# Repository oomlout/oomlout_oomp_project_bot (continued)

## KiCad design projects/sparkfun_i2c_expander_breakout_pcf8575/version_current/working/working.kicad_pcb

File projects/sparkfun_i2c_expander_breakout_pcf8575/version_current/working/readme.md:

# OOMP Project  
## I2C_Expander_Breakout-PCF8575  by sparkfun  
  
oomp key: oomp_projects_flat_sparkfun_i2c_expander_breakout_pcf8575  
(snippet of original readme)  
  
SparkFun I2C Expander Breakout - PCF8575  
========================================  

[*SparkFun I2C Expander Breakout - PCF8575 (BOB-08130)*](https://www.sparkfun.com/products/8130)  
  
This great IC allows the user to expand up to 16 I/O using only two I/O for control!   
The PCF8575C is controlled through an I2C interface and features 16-bits of quasi-bidirectional input/output pins.  
  
Repository Contents  
-------------------  
  
* **/Firmware** - Example code   
* **/Hardware** - Eagle design files (.brd, .sch)  
* **/Production** - Production panel files (.brd)  
  
Documentation  
--------------  
* **[SparkFun Fritzing repo](https://github.com/sparkfun/Fritzing_Parts)** - Fritzing diagrams for SparkFun products.  
* **[SparkFun 3D Model repo](https://github.com/sparkfun/3D_Models)** - 3D models of SparkFun products.   

License Information  
-------------------  
This product is _**open source**_!   
  
The **hardware** is released under [Creative Commons ShareAlike 4.0 International](https://creativecommons.org/licenses/by-sa/4.0/).  
  
The **code** is beerware; if you see me (or any other SparkFun employee) at the local, and you've found our code helpful, please buy us a round!  
  
Please use, reuse, and modify these files as you see fit. Please maintain attribution to SparkFun Electronics and release anything derivative under the same license.  
  
Distributed as-is; no warranty is given.  
  
- Your friends at S  
  full source readme at [readme_src.md](readme_src.md)  
  
source repo at: [https://github.com/sparkfun/I2C_Expander_Breakout-PCF8575](https://github.com/sparkfun/I2C_Expander_Breakout-PCF8575)  
## Board  

## Schematic  

[schematic pdf](working_schematic.pdf)  
## Images

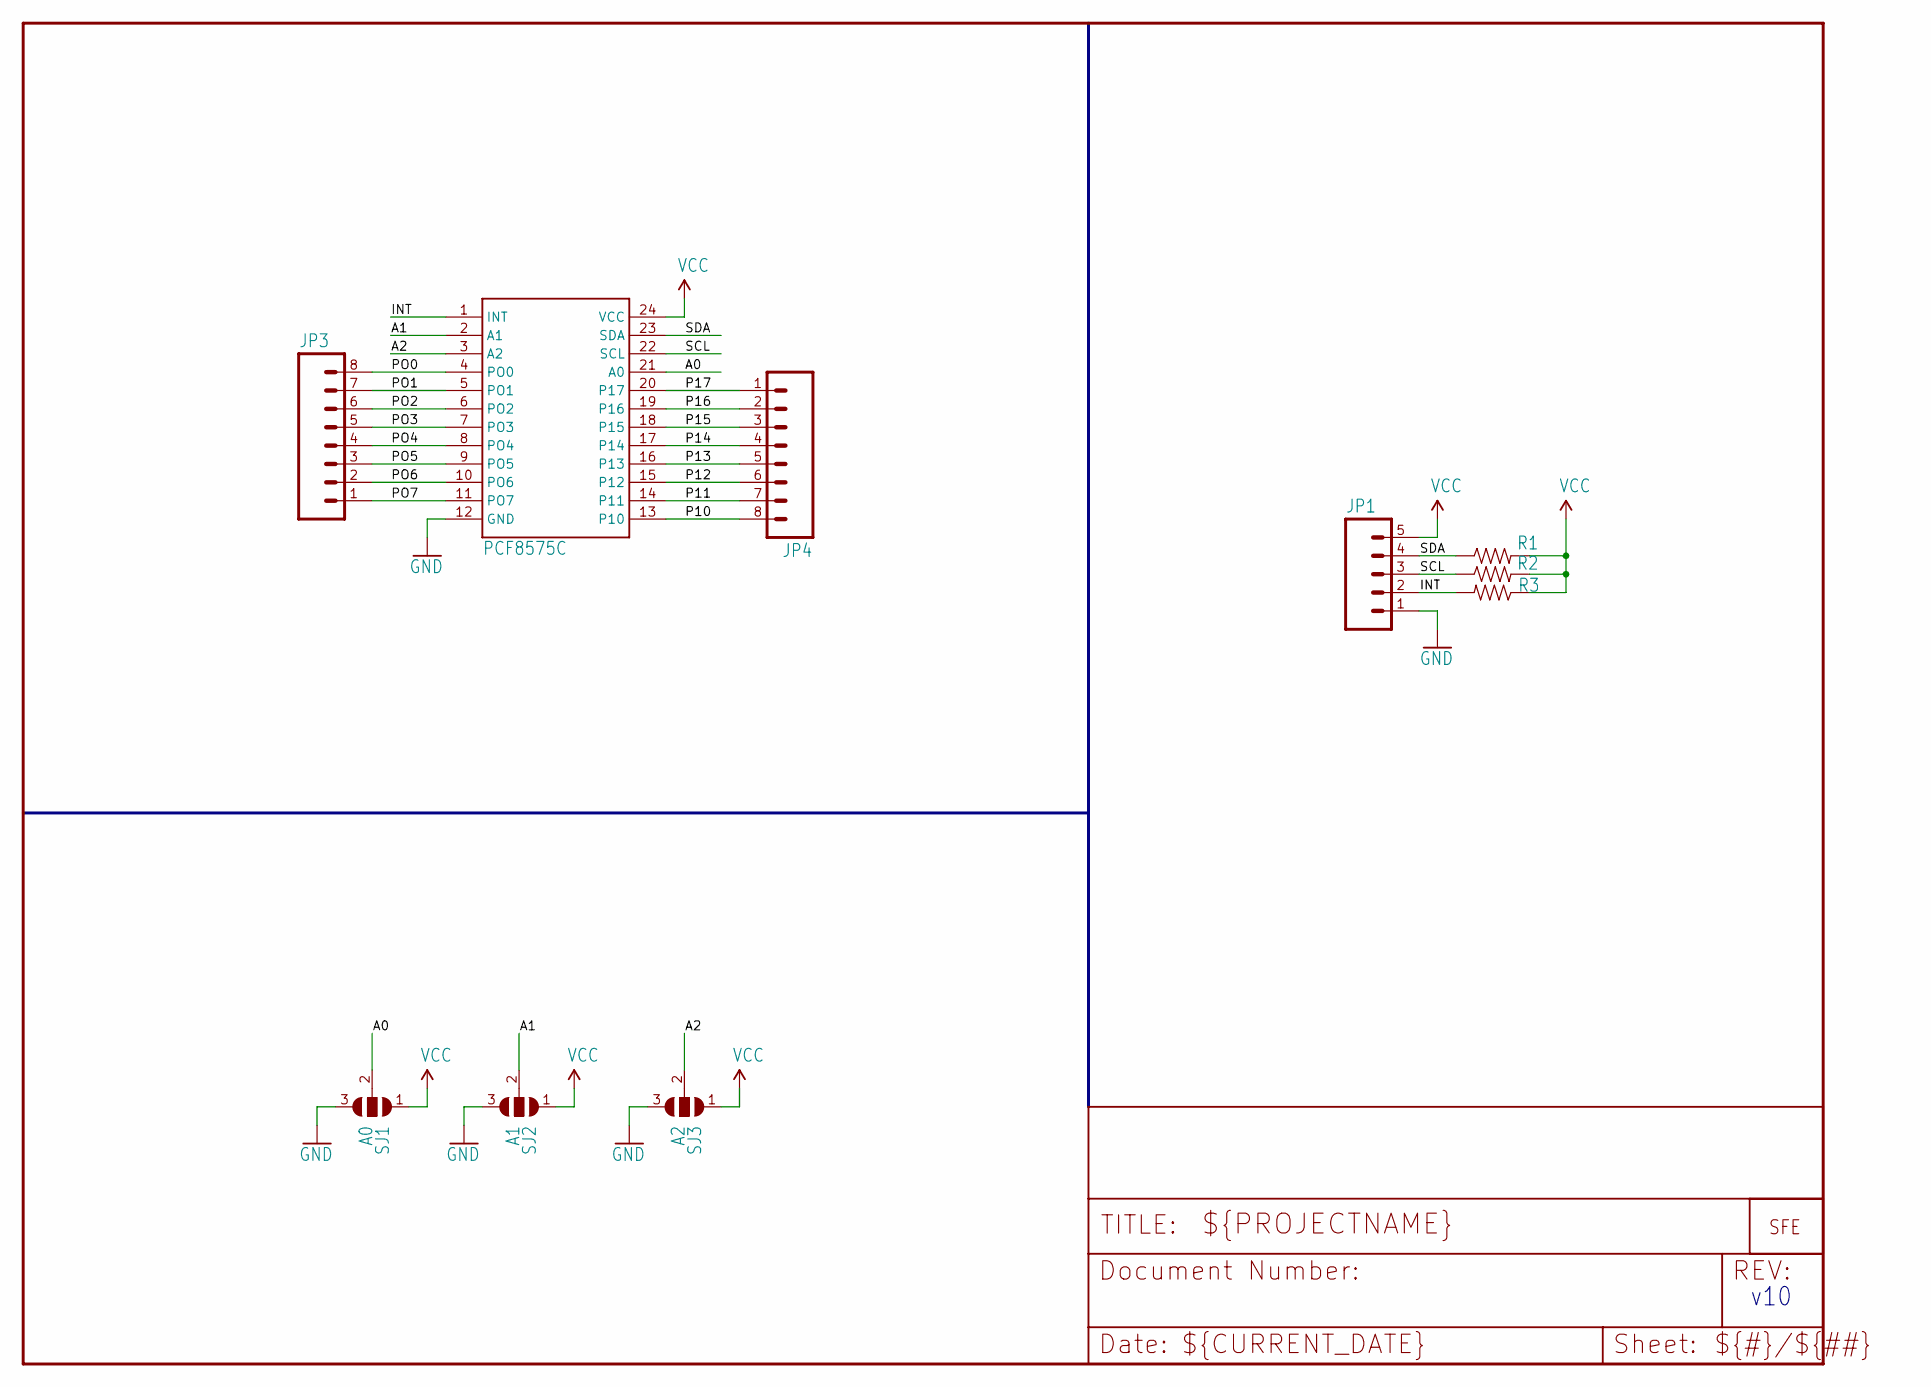
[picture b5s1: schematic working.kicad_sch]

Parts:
JP1: M05; 1X05
JP3, JP4: M08; 1X08
R1, R2, R3: RESISTOR0402; C0402
SJ1: A0; SJ_3
SJ2: A1; SJ_3
SJ3: A2; SJ_3
U1: PCF8575C; SO-24DW
U$2: LOGO-SFENEW; SFE-NEW-WEBLOGO

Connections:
A0: SJ1.2, U1.21 (A0)
A1: SJ2.2, U1.2 (A1)
A2: SJ3.2, U1.3 (A2)
GND: JP1.1, SJ1.3, SJ2.3, SJ3.3, U1.12 (GND)
INT: JP1.2, R3.2, U1.1 (INT)
P10: JP4.8, U1.13 (P10)
P11: JP4.7, U1.14 (P11)
P12: JP4.6, U1.15 (P12)
P13: JP4.5, U1.16 (P13)
P14: JP4.4, U1.17 (P14)
P15: JP4.3, U1.18 (P15)
P16: JP4.2, U1.19 (P16)
P17: JP4.1, U1.20 (P17)
PO0: JP3.8, U1.4 (PO0)
PO1: JP3.7, U1.5 (PO1)
PO2: JP3.6, U1.6 (PO2)
PO3: JP3.5, U1.7 (PO3)
PO4: JP3.4, U1.8 (PO4)
PO5: JP3.3, U1.9 (PO5)
PO6: JP3.2, U1.10 (PO6)
PO7: JP3.1, U1.11 (PO7)
SCL: JP1.3, R2.1, U1.22 (SCL)
SDA: JP1.4, R1.1, U1.23 (SDA)
VCC: JP1.5, R1.2, R2.2, R3.1, SJ1.1, SJ2.1, SJ3.1, U1.24 (VCC)

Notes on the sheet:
v10

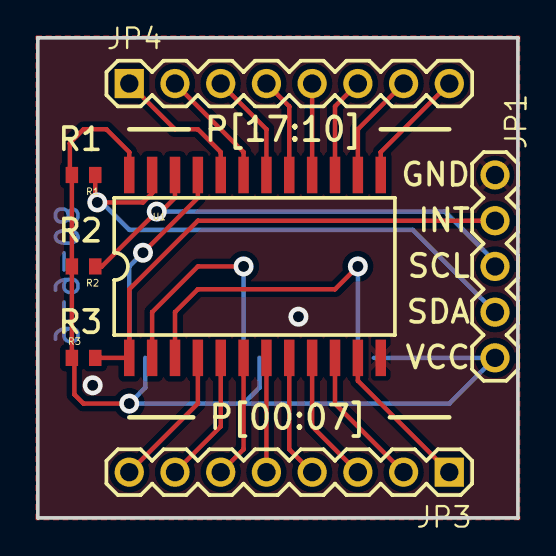
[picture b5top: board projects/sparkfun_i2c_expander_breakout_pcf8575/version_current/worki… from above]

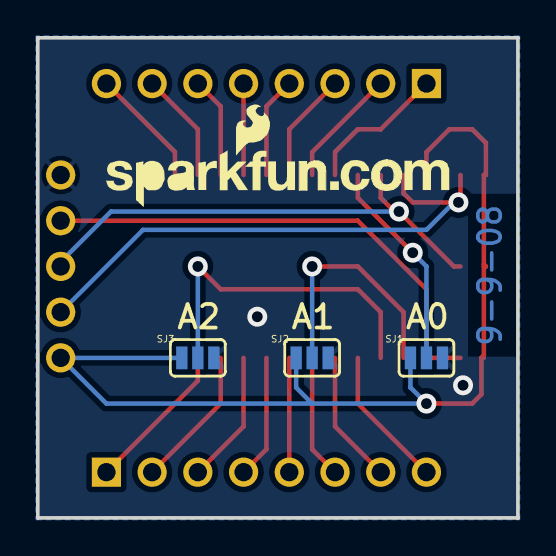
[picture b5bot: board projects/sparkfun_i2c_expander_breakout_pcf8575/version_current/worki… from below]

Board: 2 copper layers, 26.7 x 26.7 mm, 11 parts (4 on the bottom side), 24 nets.

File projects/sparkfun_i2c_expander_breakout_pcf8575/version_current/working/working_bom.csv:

Row,Description,Part,References,Value,Footprint,Quantity Per PCB,Status,Datasheet
1,,M05,JP1,M05,1X05,1, ,
2,,M08,JP3 JP4,M08,1X08,2, ,
3,,RESISTOR0402,R1 R2 R3,RESISTOR0402,C0402,3, ,
4,,PCF8575C,U1,PCF8575C,SO-24DW,1, ,
5,,LOGO-SFENEW,U$2,LOGO-SFENEW,SFE-NEW-WEBLOGO,1, ,





Project info:
Schematic:,working
Variant:,default
Revision:,
Date:,2023-08-06_12-56-03
KiCad Version:,7.0.6-7.0.6~ubuntu22.04.1
Statistics:
Component Groups:,5
Component Count:,8 (0 SMD/ 0 THT)
Fitted Components:,8 (0 SMD/ 0 THT)
Number of PCBs:,1
Total Components:,8

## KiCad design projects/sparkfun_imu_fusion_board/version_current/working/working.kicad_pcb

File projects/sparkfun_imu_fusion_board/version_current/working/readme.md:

# OOMP Project  
## IMU_Fusion_Board  by sparkfun  
  
oomp key: oomp_projects_flat_sparkfun_imu_fusion_board  
(snippet of original readme)  
  
SparkFun IMU Fusion Board - ADXL345 & IMU3000  
========================================  

[*SparkFun IMU Fusion Board - ADXL345 & IMU3000 (SEN-10252)*](https://www.sparkfun.com/products/10252)  
  
The IMU 3000 breakout features a 3-axis MEMS digital gyro with programmable ranges from +-250 to +-2000 degrees/sec.   
In addition, it has a secondary I2C port that interfaces with a digital accelerometer to deliver a complete 6-axis sensor output from its primary I2C port.   
The fusion output offloads the intensive motion processing computation requirements from the host processor, reducing the need for frequent polling of the motion sensor output and enabling low cost, low power microcontrollers.  
  
Repository Contents  
-------------------  
* **/Hardware** - Eagle design files (.brd, .sch)  
* **/Production** - Production panel files (.brd)  
  
Documentation  
--------------  
* **[SparkFun Fritzing repo](https://github.com/sparkfun/Fritzing_Parts)** - Fritzing diagrams for SparkFun products.  
* **[SparkFun 3D Model repo](https://github.com/sparkfun/3D_Models)** - 3D models of SparkFun products.   
  
License Information  
-------------------  
This product is _**open source**_!   
  
The **hardware** is released under [Creative Commons ShareAlike 4.0 International](https://creativecommons.org/licenses/by-sa/4.0/).  
  
Please use, reuse, and modify these files as you see fit. Please maintain attribution to   
  full source readme at [readme_src.md](readme_src.md)  
  
source repo at: [https://github.com/sparkfun/IMU_Fusion_Board](https://github.com/sparkfun/IMU_Fusion_Board)  
## Board  

## Schematic  

[schematic pdf](working_schematic.pdf)  
## Images

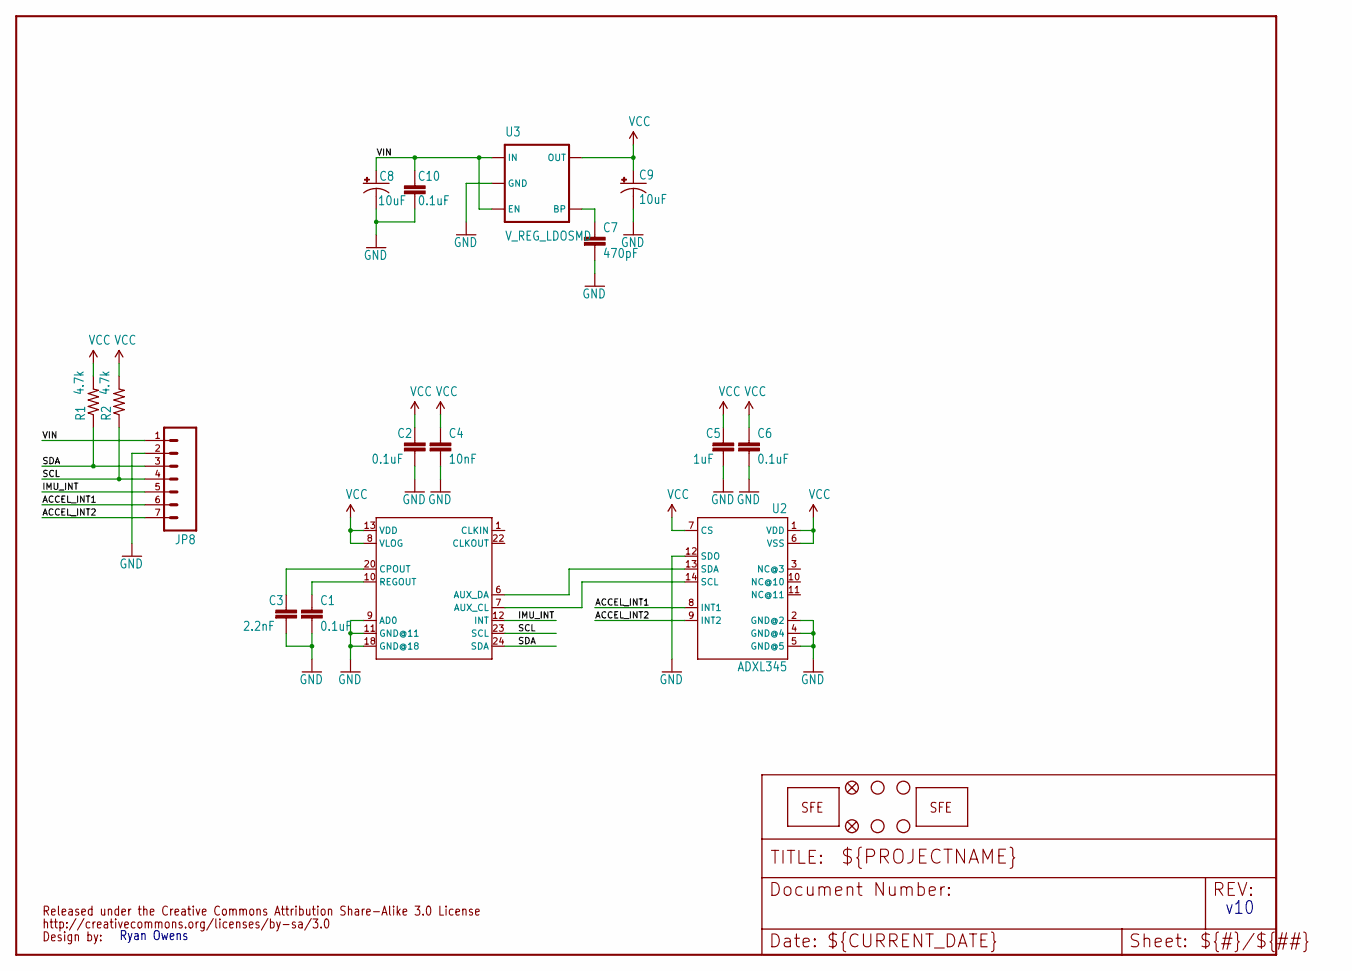
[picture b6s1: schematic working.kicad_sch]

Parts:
C1, C2, C6, C10: 0.1uF; 0603-CAP
C3: 2.2nF; 0603-CAP
C4: 10nF; 0603-CAP
C5: 1uF; 0603-CAP
C7: 470pF; 0603-CAP
C8, C9: 10uF; EIA3216
JP1: LOGO-SFENEW; SFE-NEW-WEBLOGO
JP2, JP3: FIDUCIAL1X2; FIDUCIAL-1X2
JP4, JP5, JP6, JP7: STAND-OFF
JP8: M07; 1X07
JP9: LOGO-SFESK; SFE-LOGO-FLAME
R1, R2: 4.7k; 0603-RES
U1: IMU3000; QFN-24
U2: ADXL345; LGA14
U3: V_REG_LDOSMD; SOT23-5
U$1: CREATIVE_COMMONS

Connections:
ACCEL_INT1: JP8.6, U2.8 (INT1)
ACCEL_INT2: JP8.7, U2.9 (INT2)
GND: C1.2, C2.2, C3.2, C4.2, C5.2, C6.2, C7.2, C8.C (-), C9.C (-), C10.2, JP8.2, U1.9 (AD0), U1.11 (GND@11), U1.18 (GND@18), U2.2 (GND@2), U2.4 (GND@4), U2.5 (GND@5), U2.12 (SDO), U3.2 (GND)
IMU_INT: JP8.5, U1.12 (INT)
unnamed: U1.6 (AUX_DA), U2.13 (SDA)
unnamed: C3.1, U1.20 (CPOUT)
unnamed: U1.7 (AUX_CL), U2.14 (SCL)
unnamed: C1.1, U1.10 (REGOUT)
unnamed: C7.1, U3.4 (BP)
SCL: JP8.4, R2.1, U1.23 (SCL)
SDA: JP8.3, R1.1, U1.24 (SDA)
VCC: C2.1, C4.1, C5.1, C6.1, C9.A (+), R1.2, R2.2, U1.8 (VLOG), U1.13 (VDD), U2.1 (VDD), U2.6 (VSS), U2.7 (CS), U3.5 (OUT)
VIN: C8.A (+), C10.1, JP8.1, U3.1 (IN), U3.3 (EN)

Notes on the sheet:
v10
Ryan Owens

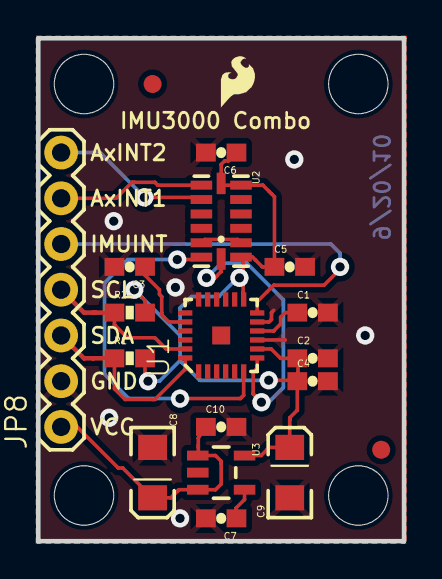
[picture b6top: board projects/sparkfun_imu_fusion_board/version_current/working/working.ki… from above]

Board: 2 copper layers, 20.3 x 27.9 mm, 25 parts (1 on the bottom side), 13 nets.

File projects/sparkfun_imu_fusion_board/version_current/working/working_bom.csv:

"Id";"Designator";"Footprint";"Quantity";"Designation";"Supplier and ref";
1;"C3";"0603-CAP";1;"2.2nF";;;
2;"C1,C6,C2,C10";"0603-CAP";4;"0.1uF";;;
3;"C5";"0603-CAP";1;"1uF";;;
4;"JP5,JP4,JP7,JP6";"STAND-OFF";4;"STAND-OFF";;;
5;"C9,C8";"EIA3216";2;"10uF";;;
6;"JP3,JP2";"FIDUCIAL-1X2";2;"FIDUCIAL1X2";;;
7;"U3";"SOT23-5";1;"3.3V";;;
8;"JP8";"1X07";1;"";;;
9;"U1";"QFN-24";1;"IMU3000";;;
10;"U$1";"CREATIVE_COMMONS";1;"CREATIVE_COMMONS";;;
11;"U2";"LGA14";1;"ADXL345";;;
12;"R2,R1";"0603-RES";2;"4.7k";;;
13;"C7";"0603-CAP";1;"470pF";;;
14;"C4";"0603-CAP";1;"10nF";;;
15;"JP9";"SFE-LOGO-FLAME";1;"LOGO-SFESK";;;
16;"JP1";"SFE-NEW-WEBLOGO";1;"LOGO-SFENEW";;;

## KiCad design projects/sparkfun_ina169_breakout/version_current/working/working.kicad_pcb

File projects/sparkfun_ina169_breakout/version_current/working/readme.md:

# INA169_Breakout by sparkfun  
This is a harvested standardized copy of a project from github.  
The original project can be found at:  
https://github.com/sparkfun/INA169_Breakout  
Please consult that link for additional, details, files, and license information.  
Note: It was auto harvested and if the original repo had more than one board file or anything out of the ordinary the files here are likely not representative.

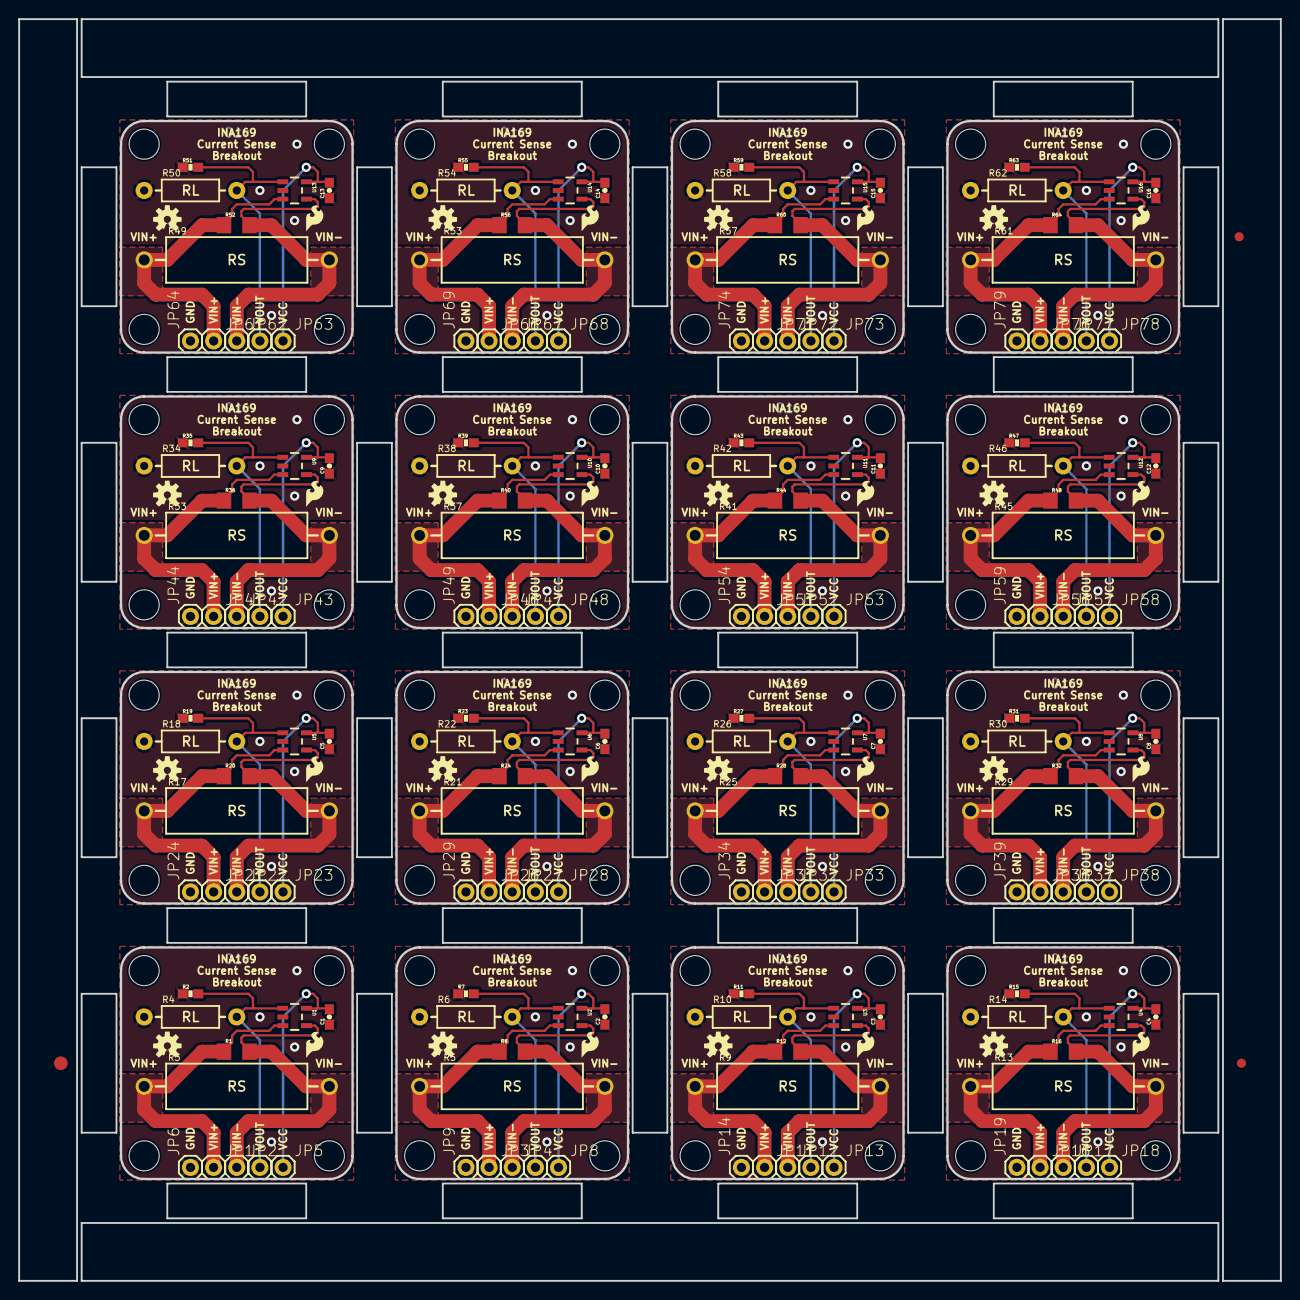
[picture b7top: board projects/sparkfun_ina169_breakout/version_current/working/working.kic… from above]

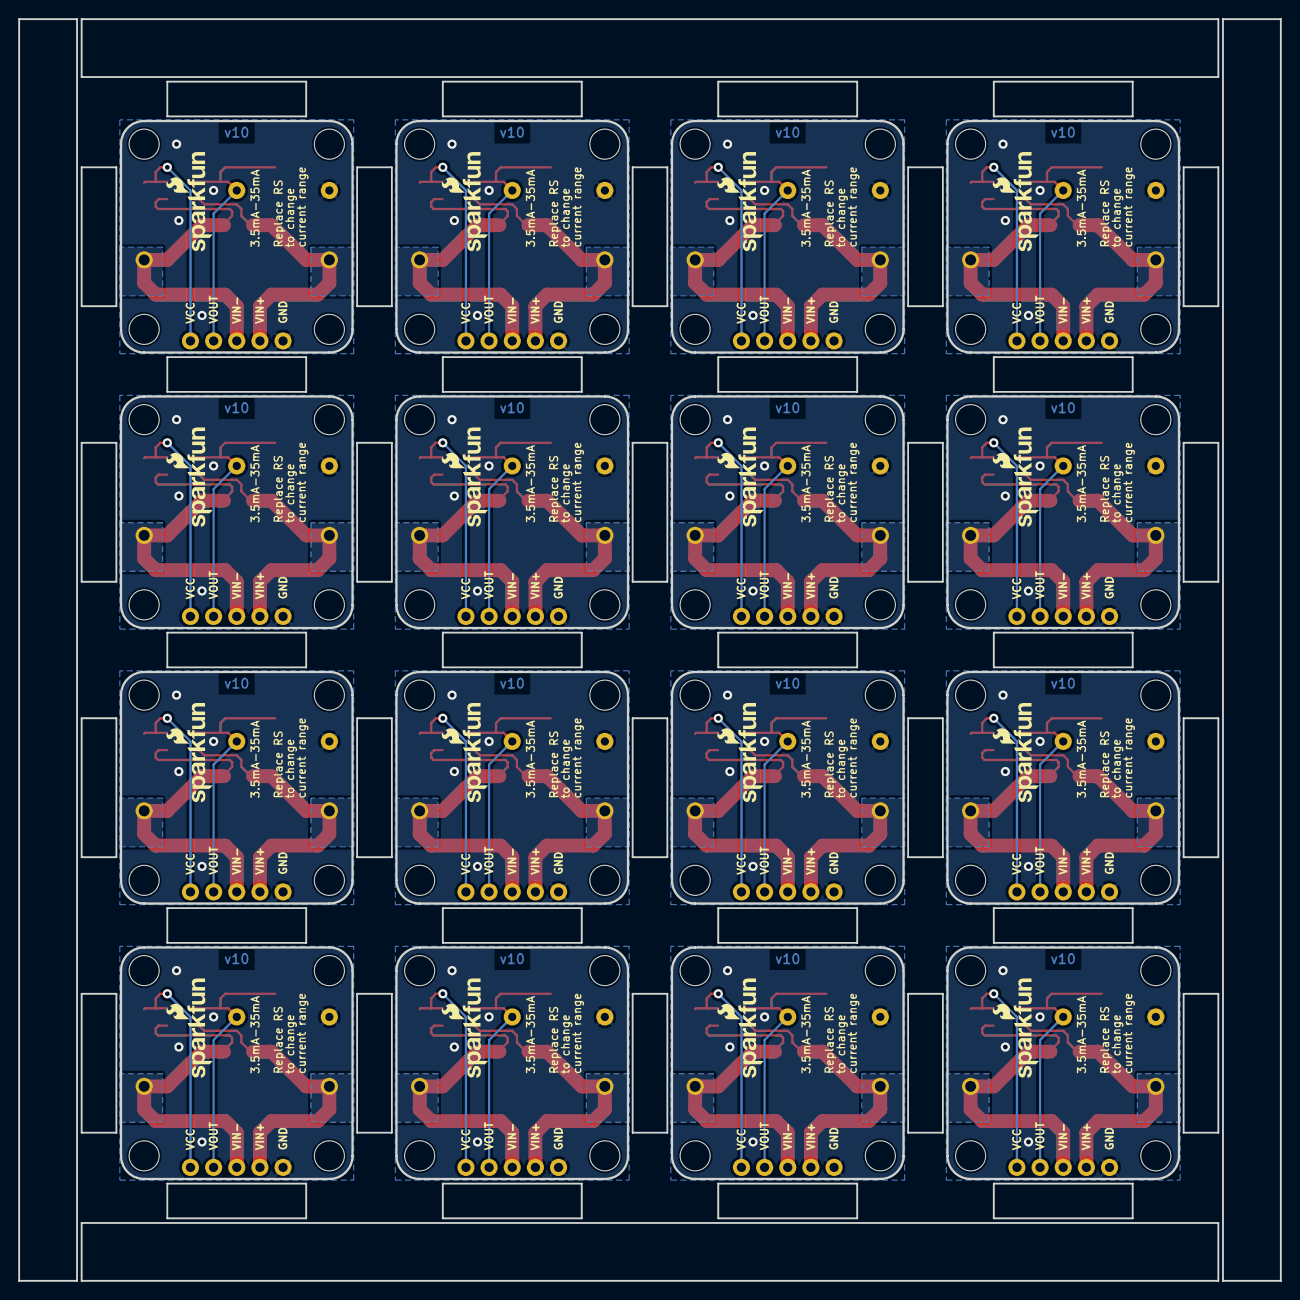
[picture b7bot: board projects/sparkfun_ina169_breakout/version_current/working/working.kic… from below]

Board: 2 copper layers, 138.4 x 138.4 mm, 291 parts (16 on the bottom side), 80 nets.

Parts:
C1, C2, C3, C4, C5, C6, C7, C8, C9, C10, C11, C12, C13, C14, C15, C16: 0.1uF; 0603-CAP
E$1: FIDUCIAL-1.5X3
E$4, E$5: FIDUCIAL-1X2
JP1, JP2, JP3, JP4, JP5, JP6, JP7, JP8, JP9, JP10, JP11, JP12, JP13, JP14, JP15, JP16, JP17, JP18, JP19, JP20, JP21, JP22, JP23, JP24, JP25, JP26, JP27, JP28, JP29, JP30, JP31, JP32, JP33, JP34, JP35, JP36, JP37, JP38, JP39, JP40, JP41, JP42, JP43, JP44, JP45, JP46, JP47, JP48, JP49, JP50, JP51, JP52, JP53, JP54, JP55, JP56, JP57, JP58, JP59, JP60, JP61, JP62, JP63, JP64, JP65, JP66, JP67, JP68, JP69, JP70, JP71, JP72, JP73, JP74, JP75, JP76, JP77, JP78, JP79, JP80: M01PTH; 1X01
LOGO1, LOGO4, LOGO7, LOGO10, LOGO13, LOGO16, LOGO19, LOGO22, LOGO25, LOGO28, LOGO31, LOGO34, LOGO37, LOGO40, LOGO43, LOGO46: SFE_LOGO_NAME_FLAME.1_INCH; SFE_LOGO_NAME_FLAME_.1
LOGO2, LOGO5, LOGO8, LOGO11, LOGO14, LOGO17, LOGO20, LOGO23, LOGO26, LOGO29, LOGO32, LOGO35, LOGO38, LOGO41, LOGO44, LOGO47: OSHW-LOGOS; OSHW-LOGO-S
LOGO3, LOGO6, LOGO9, LOGO12, LOGO15, LOGO18, LOGO21, LOGO24, LOGO27, LOGO30, LOGO33, LOGO36, LOGO39, LOGO42, LOGO45, LOGO48: LOGO-SFESK; SFE-LOGO-FLAME
R1, R8, R12, R16, R20, R24, R28, R32, R36, R40, R44, R48, R52, R56, R60, R64: 10; 1206
R2, R7, R11, R15, R19, R23, R27, R31, R35, R39, R43, R47, R51, R55, R59, R63: 10k; 0603-RES
R3, R5, R9, R13, R17, R21, R25, R29, R33, R37, R41, R45, R49, R53, R57, R61: AXIAL-0.8
R4, R6, R10, R14, R18, R22, R26, R30, R34, R38, R42, R46, R50, R54, R58, R62: AXIAL-0.4
STANDOFF1, STANDOFF2, STANDOFF3, STANDOFF4, STANDOFF5, STANDOFF6, STANDOFF7, STANDOFF8, STANDOFF9, STANDOFF10, STANDOFF11, STANDOFF12, STANDOFF13, STANDOFF14, STANDOFF15, STANDOFF16, STANDOFF17, STANDOFF18, STANDOFF19, STANDOFF20, STANDOFF21, STANDOFF22, STANDOFF23, STANDOFF24, STANDOFF25, STANDOFF26, STANDOFF27, STANDOFF28, STANDOFF29, STANDOFF30, STANDOFF31, STANDOFF32, STANDOFF33, STANDOFF34, STANDOFF35, STANDOFF36, STANDOFF37, STANDOFF38, STANDOFF39, STANDOFF40, STANDOFF41, STANDOFF42, STANDOFF43, STANDOFF44, STANDOFF45, STANDOFF46, STANDOFF47, STANDOFF48, STANDOFF49, STANDOFF50, STANDOFF51, STANDOFF52, STANDOFF53, STANDOFF54, STANDOFF55, STANDOFF56, STANDOFF57, STANDOFF58, STANDOFF59, STANDOFF60, STANDOFF61, STANDOFF62, STANDOFF63, STANDOFF64: STAND-OFF
U1, U2, U3, U4, U5, U6, U7, U8, U9, U10, U11, U12, U13, U14, U15, U16: INA169; SOT23-5

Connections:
GND: C1.1, JP6.1, R2.1, R4.P$1, U1.2
GND1: C2.1, JP9.1, R6.P$1, R7.1, U2.2
GND2: C3.1, JP14.1, R10.P$1, R11.1, U3.2
GND3: C4.1, JP19.1, R14.P$1, R15.1, U4.2
GND4: C5.1, JP24.1, R18.P$1, R19.1, U5.2
GND5: C6.1, JP29.1, R22.P$1, R23.1, U6.2
GND6: C7.1, JP34.1, R26.P$1, R27.1, U7.2
GND7: C8.1, JP39.1, R30.P$1, R31.1, U8.2
GND8: C9.1, JP44.1, R34.P$1, R35.1, U9.2
GND9: C10.1, JP49.1, R38.P$1, R39.1, U10.2
GND10: C11.1, JP54.1, R42.P$1, R43.1, U11.2
GND11: C12.1, JP59.1, R46.P$1, R47.1, U12.2
GND12: C13.1, JP64.1, R50.P$1, R51.1, U13.2
GND13: C14.1, JP69.1, R54.P$1, R55.1, U14.2
GND14: C15.1, JP74.1, R58.P$1, R59.1, U15.2
GND15: C16.1, JP79.1, R62.P$1, R63.1, U16.2
VCC: C1.2, JP5.1, U1.5
VCC1: C2.2, JP8.1, U2.5
VCC2: C3.2, JP13.1, U3.5
VCC3: C4.2, JP18.1, U4.5
VCC4: C5.2, JP23.1, U5.5
VCC5: C6.2, JP28.1, U6.5
VCC6: C7.2, JP33.1, U7.5
VCC7: C8.2, JP38.1, U8.5
VCC8: C9.2, JP43.1, U9.5
VCC9: C10.2, JP48.1, U10.5
VCC10: C11.2, JP53.1, U11.5
VCC11: C12.2, JP58.1, U12.5
VCC12: C13.2, JP63.1, U13.5
VCC13: C14.2, JP68.1, U14.5
VCC14: C15.2, JP73.1, U15.5
VCC15: C16.2, JP78.1, U16.5
VIN+: JP1.1, R1.1, R3.P$1, U1.3
VIN+1: JP3.1, R5.P$1, R8.1, U2.3
VIN+2: JP11.1, R9.P$1, R12.1, U3.3
VIN+3: JP16.1, R13.P$1, R16.1, U4.3
VIN+4: JP21.1, R17.P$1, R20.1, U5.3
VIN+5: JP26.1, R21.P$1, R24.1, U6.3
VIN+6: JP31.1, R25.P$1, R28.1, U7.3
VIN+7: JP36.1, R29.P$1, R32.1, U8.3
VIN+8: JP41.1, R33.P$1, R36.1, U9.3
VIN+9: JP46.1, R37.P$1, R40.1, U10.3
VIN+10: JP51.1, R41.P$1, R44.1, U11.3
VIN+11: JP56.1, R45.P$1, R48.1, U12.3
VIN+12: JP61.1, R49.P$1, R52.1, U13.3
VIN+13: JP66.1, R53.P$1, R56.1, U14.3
VIN+14: JP71.1, R57.P$1, R60.1, U15.3
VIN+15: JP76.1, R61.P$1, R64.1, U16.3
VIN-: JP2.1, R1.2, R3.P$2, U1.4
VIN-1: JP4.1, R5.P$2, R8.2, U2.4
VIN-2: JP12.1, R9.P$2, R12.2, U3.4
VIN-3: JP17.1, R13.P$2, R16.2, U4.4
VIN-4: JP22.1, R17.P$2, R20.2, U5.4
VIN-5: JP27.1, R21.P$2, R24.2, U6.4
VIN-6: JP32.1, R25.P$2, R28.2, U7.4
VIN-7: JP37.1, R29.P$2, R32.2, U8.4
VIN-8: JP42.1, R33.P$2, R36.2, U9.4
VIN-9: JP47.1, R37.P$2, R40.2, U10.4
VIN-10: JP52.1, R41.P$2, R44.2, U11.4
VIN-11: JP57.1, R45.P$2, R48.2, U12.4
VIN-12: JP62.1, R49.P$2, R52.2, U13.4
VIN-13: JP67.1, R53.P$2, R56.2, U14.4
VIN-14: JP72.1, R57.P$2, R60.2, U15.4
VIN-15: JP77.1, R61.P$2, R64.2, U16.4
VOUT: JP7.1, R2.2, R4.P$2, U1.1
VOUT1: JP10.1, R6.P$2, R7.2, U2.1
VOUT2: JP15.1, R10.P$2, R11.2, U3.1
VOUT3: JP20.1, R14.P$2, R15.2, U4.1
VOUT4: JP25.1, R18.P$2, R19.2, U5.1
VOUT5: JP30.1, R22.P$2, R23.2, U6.1
VOUT6: JP35.1, R26.P$2, R27.2, U7.1
VOUT7: JP40.1, R30.P$2, R31.2, U8.1
VOUT8: JP45.1, R34.P$2, R35.2, U9.1
VOUT9: JP50.1, R38.P$2, R39.2, U10.1
VOUT10: JP55.1, R42.P$2, R43.2, U11.1
VOUT11: JP60.1, R46.P$2, R47.2, U12.1
VOUT12: JP65.1, R50.P$2, R51.2, U13.1
VOUT13: JP70.1, R54.P$2, R55.2, U14.1
VOUT14: JP75.1, R58.P$2, R59.2, U15.1
VOUT15: JP80.1, R62.P$2, R63.2, U16.1

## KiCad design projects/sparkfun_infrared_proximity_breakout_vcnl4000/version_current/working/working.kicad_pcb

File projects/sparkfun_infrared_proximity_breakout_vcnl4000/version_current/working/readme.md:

# OOMP Project  
## Infrared_Proximity_Breakout-VCNL4000  by sparkfun  
  
oomp key: oomp_projects_flat_sparkfun_infrared_proximity_breakout_vcnl4000  
(snippet of original readme)  
  
**NOTE:** *This product has been retired from our catalog. If you are looking for more up-to-date info, please check out some of these resources to see how other users are still hacking and improving on this product.*  
* *[SparkFun Forum](https://forum.sparkfun.com/)*  
* *[Comments Here on GitHub](https://github.com/sparkfun/Infrared_Proximity_Breakout-VCNL4000/issues)*  
  
SparkFun Infrared Proximity Breakout - VCNL4000  
========================================  

[*SparkFun Infrared Proximity Breakout - VCNL4000 (BOB-10901)*](https://www.sparkfun.com/products/10901)  
  
The VCNL4000 can detect its proximity to an object using IR within a range of about 20cm.   
Proximity data as well as ambient light level data can be collected over an I2C interface.  
  
Repository Contents  
-------------------  
  
* **/Firmware** - Example Arduino code   
* **/Hardware** - Eagle design files (.brd, .sch)  
* **/Production** - Production panel files (.brd)  
  
Documentation  
--------------  
* **[SparkFun Fritzing repo](https://github.com/sparkfun/Fritzing_Parts)** - Fritzing diagrams for SparkFun products.  
* **[SparkFun 3D Model repo](https://github.com/sparkfun/3D_Models)** - 3D models of SparkFun products.   
  
License Information  
-------------------  
This product is _**open source**_!   
  
The **hardware** is released under [Creative Commons ShareAlike 4.0 International](https://creativecommons.org/licenses/by-s  
  full source readme at [readme_src.md](readme_src.md)  
  
source repo at: [https://github.com/sparkfun/Infrared_Proximity_Breakout-VCNL4000](https://github.com/sparkfun/Infrared_Proximity_Breakout-VCNL4000)  
## Board  

## Schematic  

[schematic pdf](working_schematic.pdf)  
## Images

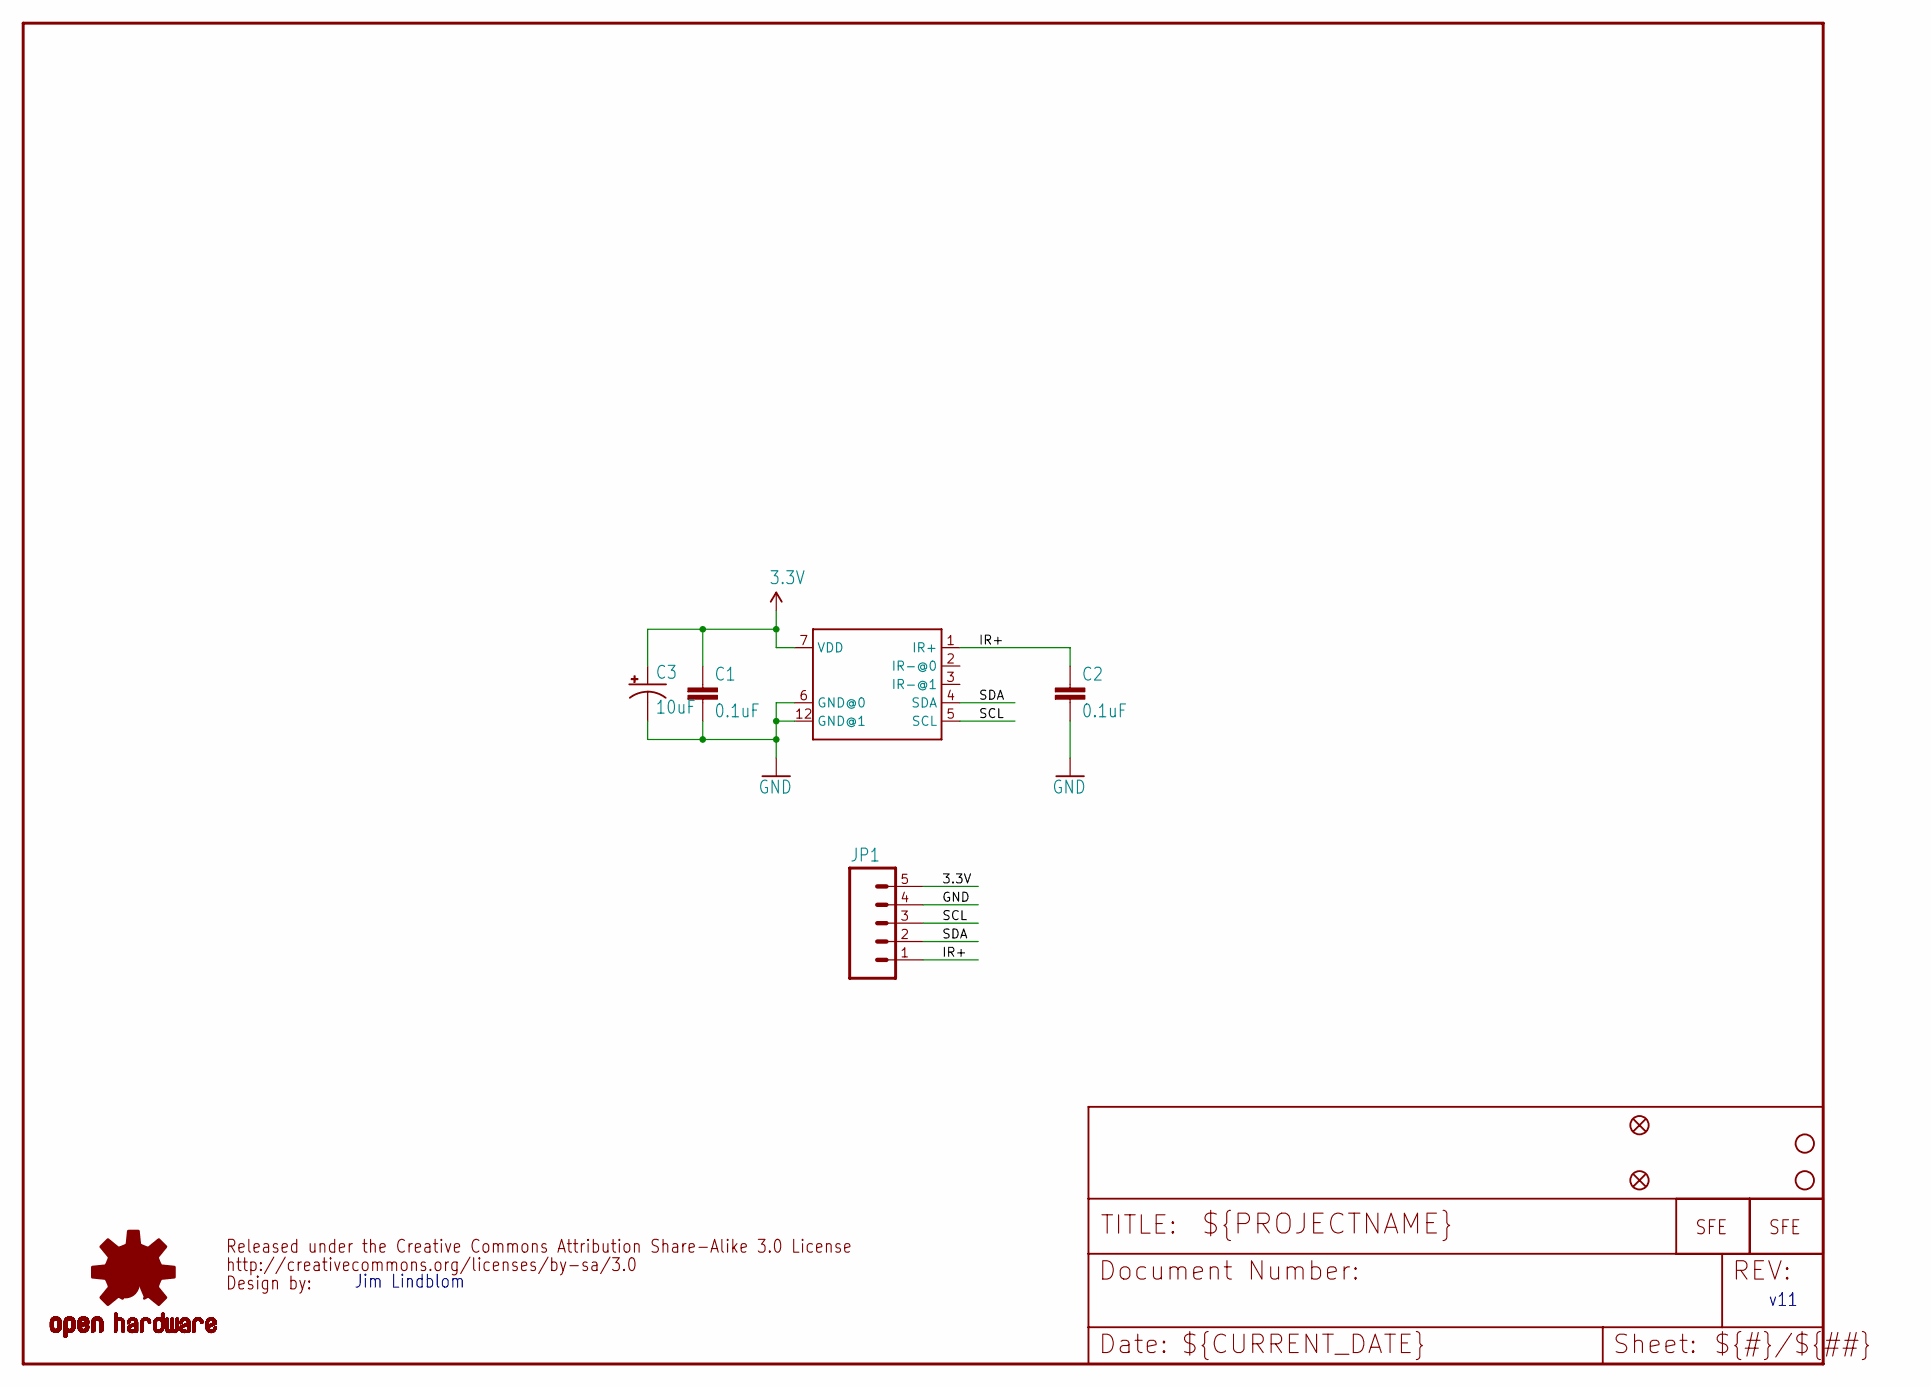
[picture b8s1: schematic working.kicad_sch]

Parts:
C1, C2: 0.1uF; 0402-CAP
C3: 10uF; EIA3216
JP1: M05PTH; 1X05
JP2: LOGO-SFENW2; SFE-NEW-WEB
JP3, JP4: STAND-OFF
JP5: LOGO-SFESK; SFE-LOGO-FLAME
JP6, JP7: FIDUCIALUFIDUCIAL; MICRO-FIDUCIAL
U1: VCNL4000
U$1: OSHW-LOGOS; OSHW-LOGO-S
U$2: CREATIVE_COMMONS

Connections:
3.3V: C1.1, C3.A (+), JP1.5, U1.7 (VDD)
GND: C1.2, C2.2, C3.C (-), JP1.4, U1.6 (GND@0), U1.12 (GND@1)
IR+: C2.1, JP1.1, U1.1 (IR+)
SCL: JP1.3, U1.5 (SCL)
SDA: JP1.2, U1.4 (SDA)

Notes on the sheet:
Jim Lindblom
v11

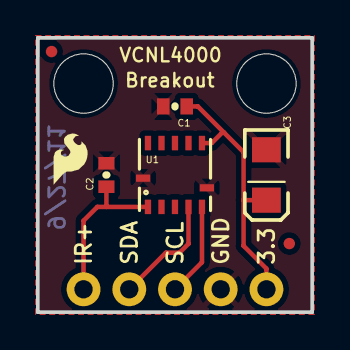
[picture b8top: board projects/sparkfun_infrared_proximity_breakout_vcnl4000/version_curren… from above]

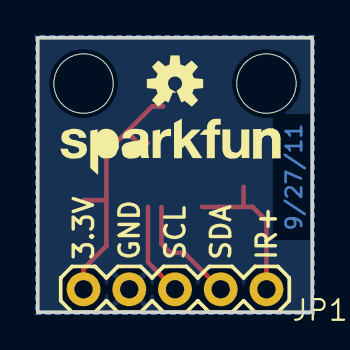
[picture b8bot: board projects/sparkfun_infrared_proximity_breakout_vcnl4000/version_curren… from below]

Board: 2 copper layers, 15.2 x 15.2 mm, 13 parts (3 on the bottom side), 5 nets.
